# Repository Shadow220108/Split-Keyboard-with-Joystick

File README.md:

# Split-Keyboard-with-Joystick

Its a split keyboard custom designed for most effective use ( for me ) with an integrated joystick ( to be used as cursor) , maximizing productivity and ergonomics  
I am using XIAO NRF58240 rather than ESP32 cause the zmk firmware support is currently experimental/non-existent in the main branch, and the battery life of the keyboard which will be reduced to days rather than months in NRF58240

# HERE IS THE DESIGN OF SPLIT KEYBOARD

# HERE IS THE CASE ( WHICH WILL BE 3D PRINTED )

# HERE IS THE PCB DESIGN

# HERE IS THE LEFT HALF SCHEMATIC

# HERE IS THE RIGHT HALF SCHEMATIC

# Firmware
For firmware , i will be using ZMK the files used for them are in the folder i will be flashing it after the build

# BOM 
|ITEM                                 |DESCRIPTION    |QUANTITY                    |UNIT PRICE|TOTAL PRICE|URL                                                                                                                               |RUNNING TOTAL ( with tax )                |
|-------------------------------------|---------------|----------------------------|----------|-----------|----------------------------------------------------------------------------------------------------------------------------------|------------------------------------------|
|                                     |               |                            |          |           |                                                                                                                                  |                                          |
|PCB MANUFACTURE                      |PCB            |5(minimum on jlpcb)         |3.50$     |17.50$     |https://cart.jlcpcb.com/quote?stencilLayer=2&stencilWidth=100&stencilLength=100&stencilCounts=5&spm=Jlcpcb.Homepage.1010          |24.50$                                    |
|                                     |               |                            |          |           |                                                                                                                                  |                                          |
|Seeed XIAO nRF52840                  |MICROCONTROLLER|2 ( one left and one right )|12.50$    |25$        |https://robocraze.com/products/seeed-studio-xiao-nrf52840-development-board-supports-bluetooth-5-0                                |49.50$                                    |
|                                     |               |                            |          |           |                                                                                                                                  |                                          |
|Kailh MX Hotswap Sockets             |SWITCH SOCKETS |Set of 50                   |0.10$     |5$         |https://meckeys.com/shop/accessories/keyboard-accessories/key-switches/kailh-hot-swap-socket/                                     |54.50$                                    |
|                                     |               |                            |          |           |                                                                                                                                  |                                          |
|Cherry MX Switches                   |SWITCH         |Set of 50                   |0.36$     |18$        |https://meckeys.com/shop/accessories/keyboard-accessories/key-switches/cherry-mx-rgb-switch/                                      |72.50$                                    |
|                                     |               |                            |          |           |                                                                                                                                  |                                          |
|Blank Keycaps 1.0u                   |KEYCAPS        |Set of 50                   |0.20$     |10$        |https://meckeys.com/shop/accessories/keyboard-accessories/keycaps/blank-dsa-keycaps-1u/                                           |82.50$                                    |
|                                     |               |                            |          |           |                                                                                                                                  |                                          |
|3.7V LiPo Batteries                  |BATTERIES      |2 ( one left and one right )|1$        |3$         |https://quartzcomponents.com/products/3-7v-1000mah-li-po-rechargeable-battery?variant=44131981295850                              |85.10$                                    |
|                                     |               |                            |          |           |                                                                                                                                  |                                          |
|1N4148 - Fast Switching Diode SOD-323|DIODES         |50                          |0.02$     |1.0$      |https://quartzcomponents.com/products/1n4148ws-t4-switching-diode-sod-123-smd-package?variant=45540031627498                      |86$                                       |
|                                     |               |                            |          |           |                                                                                                                                  |                                          |
|74HC165                              |SHIFT REGISTOR |1                           |0.2$        |0.2$         |https://quartzcomponents.com/products/74hc165-ic-8-bit-parallel-in-serial-out-shift-register-ic-smd-package?variant=44714752901354|86$                                       |
|                                     |               |                            |          |           |                                                                                                                                  |                                          |
|SK16812 MINI                         |LED            |10                          |          |           |                                                                                                                                  |self sourced                              |
|                                     |               |                            |          |           |                                                                                                                                  |                                          |
|Joystick and breakout board          |Joystick       |1                           |0.40$     |0.40$      |https://robu.in/product/joystick-module-ps2-breakout-sensor/                                                                      |87.00$                                    |
|                                     |               |                            |          |           |                                                                                                                                  |                                          |
|                                     |               |                            |          |           |TOTAL                                                                                                                             |90$ approximate with shipping and 3d parts|

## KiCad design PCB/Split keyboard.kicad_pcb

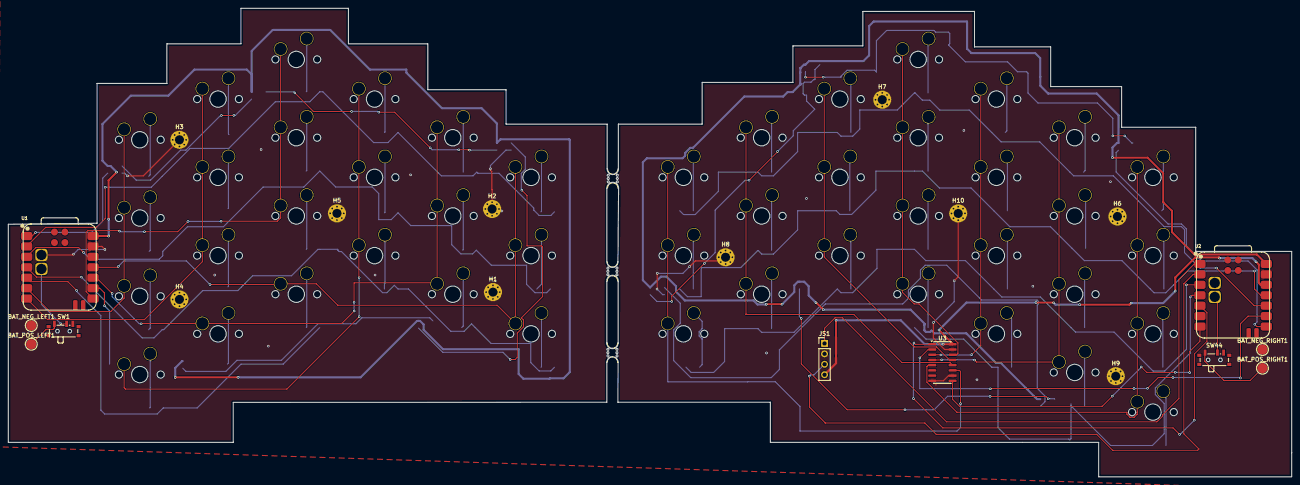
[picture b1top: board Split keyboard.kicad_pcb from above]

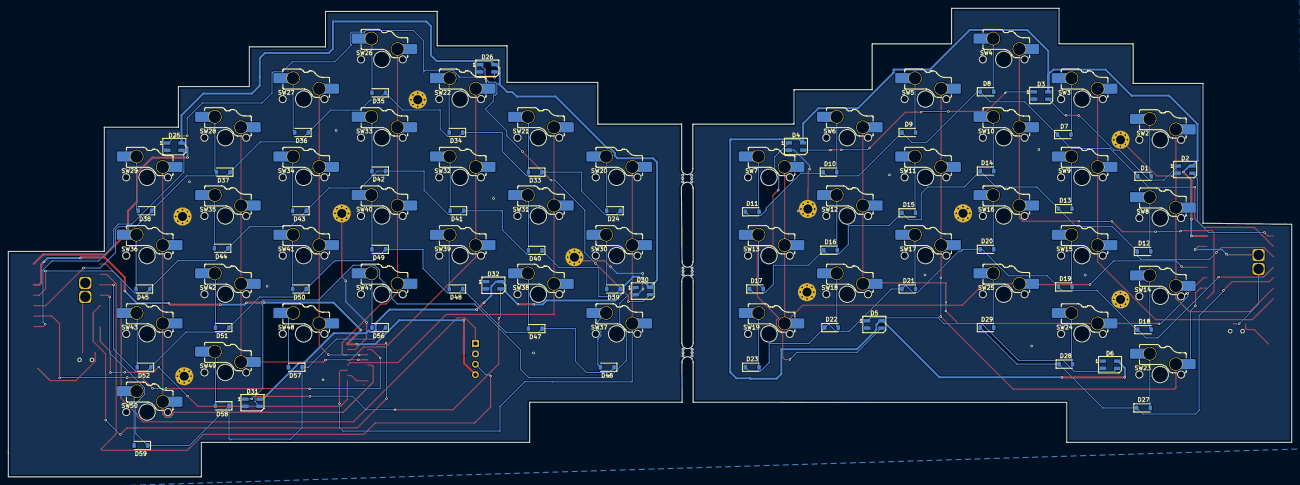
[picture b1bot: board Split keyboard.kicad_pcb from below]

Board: 2 copper layers, 312.4 x 114.0 mm, 125 parts (102 on the bottom side), 89 nets.

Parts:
BAT_NEG_LEFT1: TestPoint; TestPoint_Pad_D2.5mm
BAT_NEG_RIGHT1: TestPoint; TestPoint_Pad_D2.5mm
BAT_POS_LEFT1: TestPoint; TestPoint_Pad_D2.5mm
BAT_POS_RIGHT1: TestPoint; TestPoint_Pad_D2.5mm
D1, D7, D8, D9, D10, D11, D12, D13, D14, D15, D16, D17, D18, D19, D20, D21, D22, D23, D24, D27, D28, D29, D33, D34, D35, D36, D37, D38, D39, D40, D41, D42, D43, D44, D45, D46, D47, D48, D49, D50, D51, D52, D56, D57, D58, D59: 1N5819; D_SOD-123
D2, D3, D4, D5, D6, D25, D26, D30, D31, D32: SK6812MINI; LED_SK6812MINI_PLCC4_3.5x3.5mm_P1.75mm
H1, H2, H3, H4, H5, H6, H7, H8, H9, H10: MountingHole_Pad; MountingHole_2.2mm_M2_Pad_Via
H11, H12, H13: Break off; mouse-bite-2.54mm-slot
JS1: joystick_analog; PinHeader_1x04_P2.54mm_Vertical
SW1, SW44: SW_SPDT; SW_SPDT_PCM12
SW2, SW3, SW4, SW5, SW6, SW7, SW8, SW9, SW10, SW11, SW12, SW13, SW14, SW15, SW16, SW17, SW18, SW19, SW20, SW21, SW22, SW23, SW24, SW25, SW26, SW27, SW28, SW29, SW30, SW31, SW32, SW33, SW34, SW35, SW36, SW37, SW38, SW39, SW40, SW41, SW42, SW43, SW47, SW48, SW49, SW50: SW_Push; SW_MX_HS_KS-2P02B01-01_1u
U1, U2: XIAO-nRF52840-SMD; modified-XIAO-nRF52840-SMD
U3: 74HC165; SOIC-16_3.9x9.9mm_P1.27mm

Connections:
+5V: D2.4 (VDD), D3.4 (VDD), D4.4 (VDD), D5.4 (VDD), D6.4 (VDD), D25.4 (VDD), D26.4 (VDD), D30.4 (VDD), D31.4 (VDD), D32.4 (VDD), U1.14 (5V), U2.14 (5V)
/left_half/COL1: SW2.1, SW8.1, SW14.1, U1.6 (P0.05_A5_D5_SCL)
/left_half/COL2: SW3.1, SW9.1, SW15.1, U1.7 (P1.11_D6_TX)
/left_half/COL3: SW4.1, SW10.1, SW16.1, U1.8 (P1.12_D7_RX)
/left_half/COL4: SW5.1, SW11.1, SW17.1, SW23.1, U1.9 (P1.13_D8_SCK)
/left_half/COL5: SW6.1, SW12.1, SW18.1, SW24.1, U1.10 (P1.14_D9_MISO)
/left_half/COL6: SW7.1, SW13.1, SW19.1, SW25.1, U1.11 (P1.15_D10_MOSI)
/left_half/LED: D2.3 (DIN), U1.1 (P0.02_A0_D0)
/left_half/ROW1: D1.1 (K), D7.1 (K), D8.1 (K), D9.1 (K), D10.1 (K), D11.1 (K), U1.2 (P0.03_A1_D1)
/left_half/ROW2: D12.1 (K), D13.1 (K), D14.1 (K), D15.1 (K), D16.1 (K), D17.1 (K), U1.3 (P0.28_A2_D2)
/left_half/ROW3: D18.1 (K), D19.1 (K), D20.1 (K), D21.1 (K), D22.1 (K), D23.1 (K), U1.4 (P0.29_A3_D3)
/left_half/ROW4: D27.1 (K), D28.1 (K), D29.1 (K), U1.5 (P0.04_A4_D4_SDA)
/left_half/VBAT: SW1.2 (B), U1.15 (BAT)
/right_half/3V3: JS1.4 (VCC), U2.12 (3V3), U3.16 (VCC)
/right_half/COL1: SW20.1, SW30.1, SW37.1, U3.11 (D0)
/right_half/COL2: SW21.1, SW31.1, SW38.1, U3.12 (D1)
/right_half/COL3: SW22.1, SW32.1, SW39.1, U3.13 (D2)
/right_half/COL4: SW26.1, SW33.1, SW40.1, SW47.1, U3.14 (D3)
/right_half/COL5: SW27.1, SW34.1, SW41.1, SW48.1, U3.3 (D4)
/right_half/COL6: SW28.1, SW35.1, SW42.1, SW49.1, U3.4 (D5)
/right_half/COL7: SW29.1, SW36.1, SW43.1, SW50.1, U3.5 (D6)
/right_half/JOY_X: JS1.1 (X), U2.1 (P0.02_A0_D0)
/right_half/JOY_Y: JS1.3 (Y), U2.2 (P0.03_A1_D1)
/right_half/LED: D25.3 (DIN), U2.8 (P1.12_D7_RX)
/right_half/ROW1: D24.1 (K), D33.1 (K), D34.1 (K), D35.1 (K), D36.1 (K), D37.1 (K), D38.1 (K), U2.10 (P1.14_D9_MISO)
/right_half/ROW2: D39.1 (K), D40.1 (K), D41.1 (K), D42.1 (K), D43.1 (K), D44.1 (K), D45.1 (K), U2.11 (P1.15_D10_MOSI)
/right_half/ROW3: D46.1 (K), D47.1 (K), D48.1 (K), D49.1 (K), D50.1 (K), D51.1 (K), D52.1 (K), U2.3 (P0.28_A2_D2)
/right_half/ROW4: D56.1 (K), D57.1 (K), D58.1 (K), D59.1 (K), U2.4 (P0.29_A3_D3)
/right_half/SCK: U2.9 (P1.13_D8_SCK), U3.2 (CP)
/right_half/SR_DATA: U2.7 (P1.11_D6_TX), U3.9 (Q7)
/right_half/SR_LOAD: U2.5 (P0.04_A4_D4_SDA), U3.1 (~PL)
/right_half/VBAT: SW44.2 (B), U2.15 (BAT)
GND: BAT_NEG_LEFT1.1, BAT_NEG_RIGHT1.1, D2.2 (VSS), D3.2 (VSS), D4.2 (VSS), D5.2 (VSS), D6.2 (VSS), D25.2 (VSS), D26.2 (VSS), D30.2 (VSS), D31.2 (VSS), D32.2 (VSS), H1.1, H2.1, H3.1, H4.1, H5.1, H6.1, H7.1, H8.1, H9.1, H10.1, JS1.2 (GND), U1.13 (GND), U1.16 (GND), U2.13 (GND), U3.8 (GND), U3.10 (DS), U3.15 (~CE)
unnamed: D1.2 (A), SW2.2
unnamed: D2.1 (DOUT), D3.3 (DIN)
unnamed: D3.1 (DOUT), D4.3 (DIN)
unnamed: D4.1 (DOUT), D5.3 (DIN)
unnamed: D5.1 (DOUT), D6.3 (DIN)
unnamed: D7.2 (A), SW3.2
unnamed: D8.2 (A), SW4.2
unnamed: D9.2 (A), SW5.2
unnamed: D10.2 (A), SW6.2
unnamed: D11.2 (A), SW7.2
unnamed: D12.2 (A), SW8.2
unnamed: D13.2 (A), SW9.2
unnamed: D14.2 (A), SW10.2
unnamed: D15.2 (A), SW11.2
unnamed: D16.2 (A), SW12.2
unnamed: D17.2 (A), SW13.2
unnamed: D18.2 (A), SW14.2
unnamed: D19.2 (A), SW15.2
unnamed: D20.2 (A), SW16.2
unnamed: D21.2 (A), SW17.2
unnamed: D22.2 (A), SW18.2
unnamed: D23.2 (A), SW19.2
unnamed: D24.2 (A), SW20.2
unnamed: D25.1 (DOUT), D26.3 (DIN)
unnamed: D26.1 (DOUT), D30.3 (DIN)
unnamed: D27.2 (A), SW23.2
unnamed: D28.2 (A), SW24.2
unnamed: D29.2 (A), SW25.2
unnamed: D30.1 (DOUT), D31.3 (DIN)
unnamed: D31.1 (DOUT), D32.3 (DIN)
unnamed: D33.2 (A), SW21.2
unnamed: D34.2 (A), SW22.2
unnamed: D35.2 (A), SW26.2
unnamed: D36.2 (A), SW27.2
unnamed: D37.2 (A), SW28.2
unnamed: D38.2 (A), SW29.2
unnamed: D39.2 (A), SW30.2
unnamed: D40.2 (A), SW31.2
unnamed: D41.2 (A), SW32.2
unnamed: D42.2 (A), SW33.2
unnamed: D43.2 (A), SW34.2
unnamed: D44.2 (A), SW35.2
unnamed: D45.2 (A), SW36.2
unnamed: D46.2 (A), SW37.2
unnamed: D47.2 (A), SW38.2
unnamed: D48.2 (A), SW39.2
unnamed: D49.2 (A), SW40.2
unnamed: D50.2 (A), SW41.2
unnamed: D51.2 (A), SW42.2
unnamed: D52.2 (A), SW43.2
unnamed: D56.2 (A), SW47.2
unnamed: D57.2 (A), SW48.2
unnamed: D58.2 (A), SW49.2
unnamed: D59.2 (A), SW50.2
unnamed: BAT_POS_LEFT1.1, SW1.1 (A)
unnamed: BAT_POS_RIGHT1.1, SW44.1 (A)

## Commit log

2025-12-04 My updates
2025-12-06 Updated Joystick footprint to THT and added BOM
